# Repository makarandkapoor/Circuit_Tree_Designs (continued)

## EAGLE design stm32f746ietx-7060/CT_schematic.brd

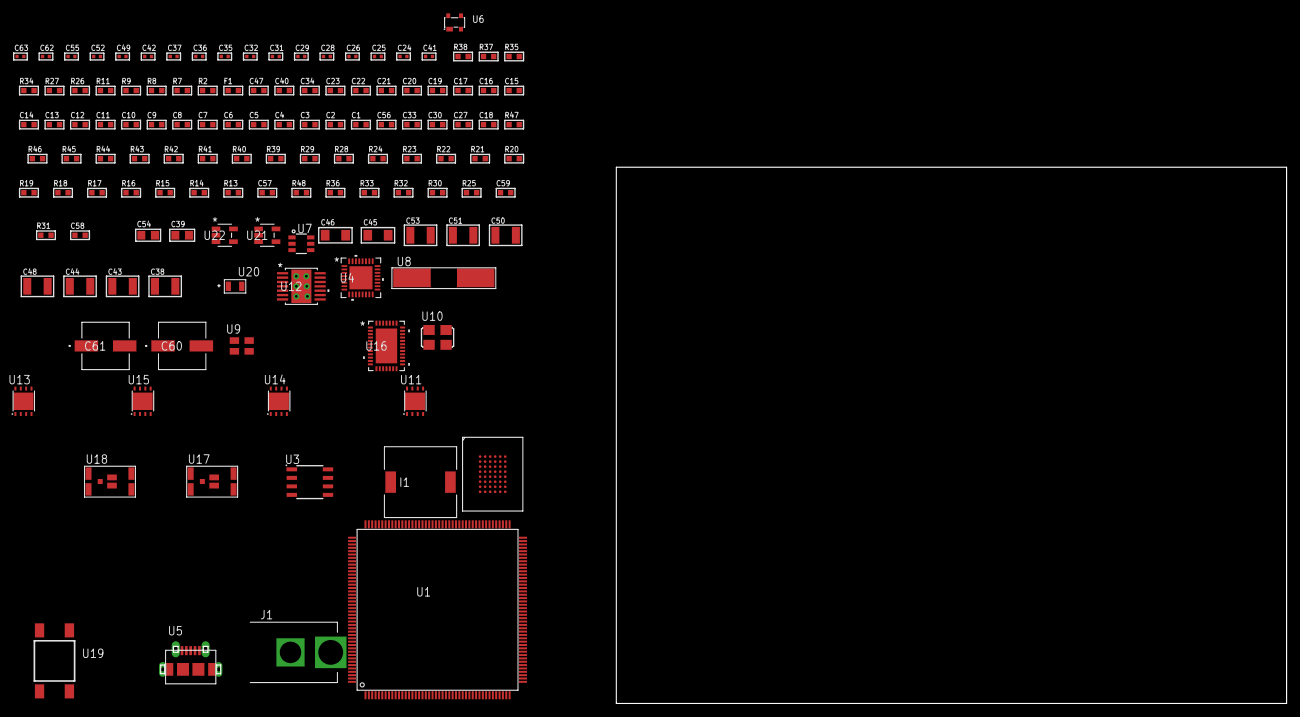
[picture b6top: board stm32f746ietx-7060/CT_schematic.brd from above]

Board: 2 copper layers, 129 parts (0 on the bottom side), 70 nets, no tracks yet.

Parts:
C1, C20, C34, C40: 1e-06; C0603
C2, C3, C4, C5, C6, C7, C8, C9, C10, C11, C12, C13, C14, C15, C16, C17, C21, C22, C23: 1e-07; C0603
C18: 4.7e-06; C0603
C19: 1e-08; C0603
C24, C25: 1e-11; C0402
C26, C29, C31, C32, C42, C55: 1e-07; C0402
C27, C30, C33, C56: 2.2e-06; C0603
C28, C35, C36, C37, C49, C52, C62, C63: 1e-08; C0402
C38, C48, C50, C51, C53: 1e-05; C1210
C39, C54: 1e-05; C0805
C41: 3.3e-09; C0402
C43, C44: 2.2e-05; C1210
C45, C46: 1e-05; C1206
C47: 8e-07; R0603
C57: 2.45e-08; R0603
C58: 2.8258362168397e-09; R0603
C59: 7.105e-09; R0603
C60, C61: 0.0001; EXV-9H
F1: 240.0; L0603
I1: 5.2e-06; DR1040
J1: PJ-037B; PJ-037B_PACKAGE
R2, R27, R35, R38: 1000.0; R0603
R7, R8: 4700.0; R0603
R9, R11: 2200.0; R0603
R13, R14, R15, R16, R17, R18, R19, R20, R21, R23, R24, R39, R41, R42, R45, R46, R47: 10000.0; R0603
R22: 47000.0; R0603
R25, R30, R32, R33, R36: 100000.0; R0603
R26, R37: 200.0; R0603
R28: 30000.0; R0603
R29: 22000.0; R0603
R31: 153694.38; R0603
R34: 3900.0; R0603
R40: 75000.0; R0603
R43, R44: 95300.0; R0603
R48: 120000.0; R0603
U1: STM32F746IET6; LQFP176
U2: IS61WV102416BLL-10MLI
U3: 24AA1025T-I/SN; SOIC-8
U4: TUSB1210BRHBR; RHB32_3P45X3P45
U5: 47590-0001; MICRO_USB_AB
U6: prtr5v0u2ax; SOT143B
U7: MAX4995AAUT+T; SOT-23-6
U8: ABLS-25.000MHZ-B2F-T
U9: ASEK-32.768KHz-ECST; ASEK
U10: ASFL1-26MHZ-NCS; ASFL1
U11, U14, U15: LP3878SDX-ADJ/NOPB; WSON-8
U12: tps54225PWP; HTSSOP14
U13: LP2951ACSDX/NOPB; WSON-8
U16: LTC2928CUHF#PBF; QFN-38_UHF
U17, U18: IRF8306MTRPbF; IRF8306MTRPBF
U19: 4-1437565-2; SW_4-1437565-2
U20: Q65110A2395; LGM67K-G1J2-24-Z
U21, U22: nc7sz125m5x; NC7SZ125M5X

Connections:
CLK_CRYSTAL_U1_29: C24.1, U1.29, U8.1
CLK_CRYSTAL_U1_30: C25.1, U1.30, U8.2
CLK_U1_9: U1.9, U9.3
CLK_U4_1: U4.1, U10.3
GND: C1.2, C2.2, C3.2, C4.2, C5.2, C6.2, C7.2, C8.2, C9.2, C10.2, C11.2, C12.2, C13.2, C14.2, C15.2, C16.2, C17.2, C18.2, C19.2, C20.2, C21.2, C22.2, C23.2, C24.2, C25.2, C26.2, C27.2, C28.2, C29.2, C30.2, C31.2, C32.2, C33.2, C34.2, C35.2, C36.2, C37.2, C38.2, C39.2, C40.2, C41.2, C43.2, C44.2, C45.2, C46.2, C47.2, C48.2, C49.2, C50.2, C51.2, C52.2, C53.2, C54.2, C55.2, C56.2, C57.2, C58.2, C59.2, C60.2, C61.2, C62.2, C63.2, J1.2, R2.2, R13.2, R21.2, R22.2, R27.2, R29.2, R32.2, R35.2, R38.2, R40.2, R43.2, R44.2, R45.2, R46.2, R47.2, U1.14, U1.22, U1.37, U1.61, U1.71, U1.90, U1.102, U1.113, U1.126, U1.135, U1.148, U1.158, U2.D1, U2.E6, U3.4, U3.7, U4.33, U5.5, U5.6, U5.7, U5.8, U5.9, U6.1, U7.2, U9.2, U10.2, U11.3, U11.PAD, U12.5, U12.8, U12.9, U12.15, U13.3, U13.4, U13.PAD, U14.3, U14.PAD, U15.3, U15.PAD, U16.8, U16.9, U16.10, U16.12, U16.13, U16.24, U16.25, U16.30, U16.32, U16.39, U20.C, U21.1, U21.3, U22.1, U22.3
NET_U1_31: R7.1, U1.31, U21.4
NET_U1_39: C19.1, C20.1, F1.1, U1.38, U1.39
NET_U1_48: R15.1, U1.48
NET_U1_125: C23.1, U1.125
NET_U1_164: R9.1, U1.164, U3.6
NET_U1_165: R11.1, U1.165, U3.5
NET_U1_166: R13.1, U1.166
NET_U1_171: R14.1, U1.171
NET_U1_176: U19.3, U19.4
NET_U2_A2: R17.1, U2.A2
NET_U2_B5: R16.1, U2.B5
NET_U2_G5: R18.1, U2.G5
NET_U3_1: R20.1, U3.1
NET_U3_2: R21.1, U3.2
NET_U3_3: R19.1, U3.3
NET_U4_11: R23.1, U4.11
NET_U4_12: C33.1, U4.12
NET_U4_14: R24.1, U4.14
NET_U4_20: C30.1, U4.20
NET_U4_27: R8.1, U4.27, U22.4
NET_U5_1: C34.1, U4.22, U5.1, U6.4, U7.1
NET_U5_2: U4.19, U5.2, U6.3
NET_U5_3: U4.18, U5.3, U6.2
NET_U5_4: U4.23, U5.4
NET_U7_3: R22.1, U7.3
NET_U7_4: U4.17, U7.4
NET_U11_1: C37.1, U11.1
NET_U11_6: R26.2, R27.1, U11.6
NET_U11_8: R25.1, U11.8
NET_U12_2: R28.2, R29.1, U12.2
NET_U12_3: C40.1, U12.3
NET_U12_4: C41.1, U12.4
NET_U12_10: C42.1, I1.1, U12.10, U12.11
NET_U12_12: C42.2, U12.12
NET_U13_5: R30.1, U13.5
NET_U13_7: R31.2, R32.1, U13.7
NET_U14_1: C49.1, U14.1
NET_U14_6: R34.2, R35.1, U14.6
NET_U14_8: R33.1, U14.8
NET_U15_1: C52.1, U15.1
NET_U15_6: R37.2, R38.1, U15.6
NET_U15_8: R36.1, U15.8
NET_U16_3: R46.1, U16.3
NET_U16_6: R43.1, U16.6
NET_U16_7: R44.1, U16.7
NET_U16_16: R45.1, R48.1, U16.16
NET_U16_18: R42.1, U16.18
NET_U16_19: R41.1, U16.19, U16.20
NET_U16_21: R39.1, R40.1, U16.21, U21.2, U22.2
NET_U16_22: C55.1, R39.2, R41.2, R42.2, U16.11, U16.22
NET_U16_26: C58.1, U16.26
NET_U16_27: C57.1, U16.27
NET_U16_28: C59.1, U16.28
NET_U16_38: R47.1, U16.38
NET_U17_3: U16.2, U17.3
NET_U18_3: U16.37, U18.3
NET_U19_1: R2.1, U19.1, U19.2
VCC_14V5: C56.1, C60.1, C61.1, J1.1, R48.2, U16.23, U17.1, U17.2, U17.6, U17.7, U18.1, U18.2, U18.6, U18.7
VCC_S1_14V5: C38.1, C45.1, C46.1, C47.1, C50.1, R25.2, R33.2, U11.4, U12.7, U12.13, U12.14, U13.8, U14.4, U17.4, U17.5
VCC_S2_14V5: C53.1, R36.2, U15.4, U18.4, U18.5
VCC_TIER1_1V2: C22.1, C39.1, R26.1, U1.81, U11.5
VCC_TIER1_1V8: C1.1, C2.1, C3.1, C4.1, C5.1, C6.1, C7.1, C8.1, C9.1, C10.1, C11.1, C12.1, C13.1, C14.1, C15.1, C16.1, C17.1, C18.1, C28.1, C31.1, C32.1, C43.1, C44.1, C62.1, C63.1, F1.2, I1.2, R7.2, R8.2, R9.2, R11.2, R14.2, R15.2, R19.2, R20.2, R23.2, R24.2, R28.1, U1.6, U1.15, U1.23, U1.36, U1.49, U1.62, U1.72, U1.82, U1.91, U1.103, U1.127, U1.136, U1.149, U1.159, U1.172, U3.8, U4.28, U4.30, U4.32, U12.1, U21.5, U22.5
VCC_TIER1_3V3: C21.1, C26.1, C27.1, C29.1, C35.1, C36.1, C48.1, R16.2, R17.2, R18.2, R30.2, R31.1, U1.114, U2.D6, U2.E1, U4.21, U9.4, U10.4, U13.1
VCC_TIER1_5V0: C51.1, R34.1, U7.5, U14.5
VCC_TIER2_1V2: C54.1, R37.1, U15.5

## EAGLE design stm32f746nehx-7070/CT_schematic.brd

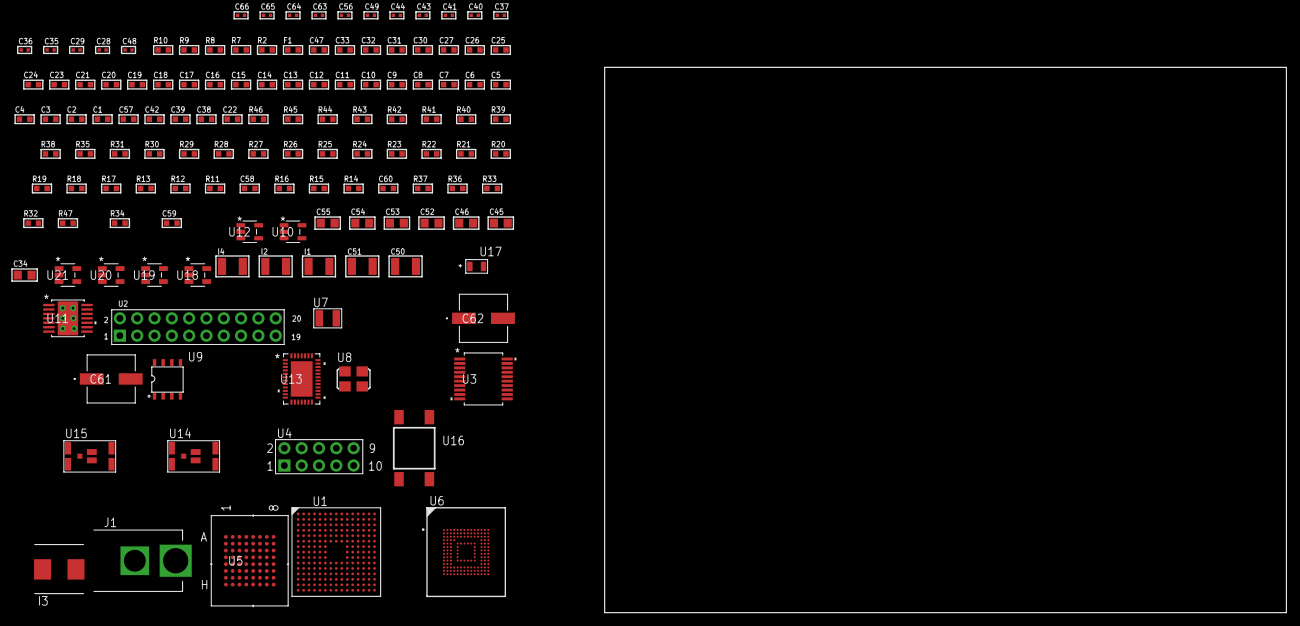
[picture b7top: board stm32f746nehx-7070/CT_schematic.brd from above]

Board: 2 copper layers, 100.0 x 80.0 mm, 135 parts (0 on the bottom side), 130 nets, no tracks yet.

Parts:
C1, C24, C30, C31, C32, C33, C47: 1e-06; C0603
C2, C3, C4, C5, C6, C7, C8, C9, C10, C11, C12, C13, C14, C15, C16, C17, C18, C19, C20, C21, C25, C26, C27: 1e-07; C0603
C22: 4.7e-06; C0603
C23: 1e-08; C0603
C28, C29: 1e-11; C0402
C34: 4.7e-06; C0805
C35, C36, C43, C44, C63, C64, C65, C66: 1e-08; C0402
C37, C40, C41, C49, C56: 1e-07; C0402
C38, C39, C42, C57: 2.2e-06; C0603
C45, C46, C52, C53, C54, C55: 1e-05; C0805
C48: 3.3e-09; C0402
C50, C51: 2.2e-05; C1210
C58: 2.45e-08; R0603
C59: 2.8258362168397e-09; R0603
C60: 7.105e-09; R0603
C61, C62: 0.0001; EXV-9H
F1: 240.0; L0603
I1, I2, I4: 1.5e-05; L1210
I3: 3.3e-06; WE-HCI_7030/7040/7050
J1: PJ-037B; PJ-037B_PACKAGE
R2: 1000.0; R0603
R7, R8, R9, R10: 4700.0; R0603
R11, R12, R13, R17, R18, R19, R20, R21, R38, R40, R41, R44, R45, R46: 10000.0; R0603
R14, R15, R16: 100000.0; R0603
R22, R23, R24, R25, R26, R27, R28, R29, R30, R31: 34000.0; R0603
R32, R33, R36, R37: 1000000.0; R0603
R34: 71007.101651032; R0603
R35: 22000.0; R0603
R39: 75000.0; R0603
R42, R43: 95300.0; R0603
R47: 36527.272727273; R0603
U1: STM32F746NEH6; TFBGA216
U2: arducam_ov2640; ARDUCAM
U3: MAX3218EAP+T; SSOP-20
U4: HTSS-105-01-G-D
U5: mt28ew512aba1HPC-0AAT; LBGA-64
U6: mtfc4gmcdm; TFBGA-153
U7: ABS07-32.768KHZ-7-T
U8: ASFL1-25MHZ-NCS; ASFL1
U9: idt74fct38072; IDT74FCT38072
U10, U12: ltc3406es5; TSOT-23-5
U11: tps54225PWP; HTSSOP14
U13: LTC2928CUHF#PBF; QFN-38_UHF
U14, U15: IRF8306MTRPbF; IRF8306MTRPBF
U16: 4-1437565-2; SW_4-1437565-2
U17: Q65110A2395; LGM67K-G1J2-24-Z
U18, U19, U20, U21: nc7sz125m5x; NC7SZ125M5X

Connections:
CLK_CRYSTAL_U1_E1: C28.1, U1.E1, U7.1
CLK_CRYSTAL_U1_F1: C29.1, U1.F1, U7.2
CLK_U1_G1: U1.G1, U9.6
CLK_U2_8: U2.8, U9.7
CLK_U9_3: U8.3, U9.3
GND: C1.2, C2.2, C3.2, C4.2, C5.2, C6.2, C7.2, C8.2, C9.2, C10.2, C11.2, C12.2, C13.2, C14.2, C15.2, C16.2, C17.2, C18.2, C19.2, C20.2, C21.2, C22.2, C23.2, C24.2, C25.2, C26.2, C27.2, C28.2, C29.2, C30.2, C31.2, C32.2, C33.2, C35.2, C36.2, C37.2, C38.2, C39.2, C40.2, C41.2, C42.2, C43.2, C44.2, C45.2, C46.1, C46.2, C47.2, C48.2, C50.2, C51.2, C52.2, C53.2, C54.2, C55.1, C55.2, C56.2, C57.2, C58.2, C59.2, C60.2, C61.2, C62.2, C63.2, C64.2, C65.2, C66.2, J1.2, R2.2, R11.2, R32.2, R35.2, R36.2, R39.2, R42.2, R43.2, R44.2, R45.2, R46.2, U1.F2, U1.F6, U1.F7, U1.F8, U1.F9, U1.F10, U1.G6, U1.G10, U1.H6, U1.H10, U1.J6, U1.J10, U1.K6, U1.K7, U1.K8, U1.K9, U1.K10, U1.L6, U1.M1, U1.N1, U2.2, U2.20, U3.5, U3.17, U3.20, U4.9, U5.E8, U5.H2, U5.H7, U6.C4, U6.E7, U6.G5, U6.H10, U6.K8, U6.N2, U6.N5, U6.P4, U6.P6, U8.2, U9.4, U9.5, U9.8, U10.2, U11.5, U11.8, U11.9, U11.15, U12.2, U13.8, U13.9, U13.10, U13.12, U13.13, U13.24, U13.25, U13.30, U13.32, U13.39, U17.C, U18.1, U18.3, U19.1, U19.3, U20.1, U20.3, U21.1, U21.3
NET_U1_E5: R12.1, U1.E5
NET_U1_E6: R11.1, U1.E6
NET_U1_E11: C27.1, U1.E11
NET_U1_J1: R9.1, U1.J1, U20.4
NET_U1_L5: R13.1, U1.L5
NET_U1_R1: C23.1, C24.1, F1.1, U1.P1, U1.R1
NET_U1_R15: U16.3, U16.4
NET_U2_19: R10.1, U2.19, U21.4
NET_U3_1: I1.1, U3.1
NET_U3_2: R14.1, U3.2
NET_U3_3: R15.1, U3.3
NET_U3_4: R16.1, U3.4
NET_U3_15: C33.1, U3.15
NET_U3_16: C34.2, U3.16
NET_U3_18: C34.1, U3.18
NET_U3_19: C32.1, U3.19
NET_U4_3: U3.12, U4.3
NET_U4_4: U3.11, U4.4
NET_U4_5: U3.14, U4.5
NET_U4_6: U3.13, U4.6
NET_U5_B4: R20.1, U5.B4
NET_U5_B5: R7.1, U5.B5, U18.4
NET_U6_C2: C39.1, C40.1, U6.C2
NET_U6_K5: R8.1, U6.K5, U19.4
NET_U10_3: I2.1, U10.3
NET_U10_5: R32.1, R33.1, U10.5
NET_U10_ATNET_3: I2.2, R33.2
NET_U11_2: R34.2, R35.1, U11.2
NET_U11_3: C47.1, U11.3
NET_U11_4: C48.1, U11.4
NET_U11_10: C49.1, I3.1, U11.10, U11.11
NET_U11_12: C49.2, U11.12
NET_U12_3: I4.1, U12.3
NET_U12_5: R36.1, R37.1, U12.5
NET_U12_ATNET_3: I4.2, R37.2
NET_U13_3: R45.1, U13.3
NET_U13_6: R42.1, U13.6
NET_U13_7: R43.1, U13.7
NET_U13_16: R44.1, R47.1, U13.16
NET_U13_18: R41.1, U13.18
NET_U13_19: R40.1, U13.19, U13.20
NET_U13_21: R38.1, R39.1, U13.21, U18.2, U19.2, U20.2, U21.2
NET_U13_26: C59.1, U13.26
NET_U13_27: C58.1, U13.27
NET_U13_28: C60.1, U13.28
NET_U13_38: R46.1, U13.38
NET_U14_3: U13.2, U14.3
NET_U15_3: U13.37, U15.3
NET_U16_1: R2.1, U16.1, U16.2
PROC_DCMI_D0: U1.E15, U2.18
PROC_DCMI_D1: U1.D15, U2.17
PROC_DCMI_D2: U1.C8, U2.16
PROC_DCMI_D3: U1.A5, U2.15
PROC_DCMI_D4: U1.E13, U2.14
PROC_DCMI_D5: U1.B6, U2.13
PROC_DCMI_D6: U1.D6, U2.12
PROC_DCMI_D7: U1.D4, U2.11
PROC_DCMI_D8: U1.D14, U2.10
PROC_DCMI_D9: U1.C14, U2.9
PROC_DCMI_HSYNC: U1.N4, U2.6
PROC_DCMI_PIXCLK: U1.P3, U2.7
PROC_DCMI_VSYNC: U1.B5, U2.5
PROC_FMC_A0: U1.D2, U5.E2
PROC_FMC_A1: U1.E2, U5.D2
PROC_FMC_A2: U1.G2, U5.C2
PROC_FMC_A3: U1.H2, U5.A2
PROC_FMC_A4: U1.J2, U5.B2
PROC_FMC_A5: U1.K3, U5.D3
PROC_FMC_A6: U1.M6, U5.C3
PROC_FMC_A7: U1.N6, U5.A3
PROC_FMC_A8: U1.P6, U5.B6
PROC_FMC_A9: U1.M8, U5.A6
PROC_FMC_A10: U1.N7, U5.C6
PROC_FMC_A11: U1.M7, U5.D6
PROC_FMC_A12: U1.M13, U5.B7
PROC_FMC_A13: U1.M12, U5.A7
PROC_FMC_A14: U1.N12, U5.C7
PROC_FMC_A15: U1.N11, U5.D7
PROC_FMC_A16: U1.N10, U5.E7
PROC_FMC_A17: U1.M10, U5.B3
PROC_FMC_A18: U1.M11, U5.C4
PROC_FMC_A19: U1.A2, U5.D5
PROC_FMC_A20: U1.A1, U5.D4
PROC_FMC_A21: U1.B1, U5.C5
PROC_FMC_A22: U1.B2, U5.B8
PROC_FMC_A23: U1.A3, U5.C8
PROC_FMC_A24: U1.B3, U5.F8
PROC_FMC_D0: U1.L12, U5.E3
PROC_FMC_D1: U1.K13, U5.H3
PROC_FMC_D2: U1.B12, U5.E4
PROC_FMC_D3: U1.C12, U5.H4
PROC_FMC_D4: U1.R8, U5.H5
PROC_FMC_D5: U1.N9, U5.E5
PROC_FMC_D6: U1.P9, U5.H6
PROC_FMC_D7: U1.R9, U5.E6
PROC_FMC_D8: U1.P10, U5.F3
PROC_FMC_D9: U1.R10, U5.G3
PROC_FMC_D10: U1.R12, U5.F4
PROC_FMC_D11: U1.P11, U5.G4
PROC_FMC_D12: U1.R11, U5.F5
PROC_FMC_D13: U1.L15, U5.G6
PROC_FMC_D14: U1.L14, U5.F6
PROC_FMC_D15: U1.K15, U5.G7
PROC_FMC_NBL0: R21.1, U1.A6, U5.F7
PROC_FMC_NE2: R17.1, U1.D9, U5.F2
PROC_FMC_NOE: R18.1, U1.D11, U5.G2
PROC_FMC_NWAIT: U1.B11, U5.A4
PROC_FMC_NWE: R19.1, U1.C10, U5.A5
PROC_SDMMC1_CK: R31.1, U1.A12, U6.M6
PROC_SDMMC1_CMD: R30.1, U1.D12, U6.M5
PROC_SDMMC1_D0: R22.1, U1.G14, U6.A3
PROC_SDMMC1_D1: R23.1, U1.F14, U6.A4
PROC_SDMMC1_D2: R24.1, U1.B14, U6.A5
PROC_SDMMC1_D3: R25.1, U1.B13, U6.B2
PROC_SDMMC1_D4: R26.1, U1.A7, U6.B3
PROC_SDMMC1_D5: R27.1, U1.B4, U6.B4
PROC_SDMMC1_D6: R28.1, U1.H15, U6.B5
PROC_SDMMC1_D7: R29.1, U1.G15, U6.B6
VCC_5V2: C56.1, C57.1, C61.1, C62.1, J1.1, R38.2, R40.2, R41.2, R47.2, U13.11, U13.22, U14.1, U14.2, U14.6, U14.7, U15.1, U15.2, U15.6, U15.7
VCC_S1_5V2: C45.1, C52.1, C53.1, U10.4, U11.7, U11.13, U11.14, U14.4, U14.5
VCC_S2_5V2: C54.1, U12.4, U15.4, U15.5
VCC_TIER1_1V2: C26.1, C46.2, I2.2, R33.2, U1.L11
VCC_TIER1_3V3: C1.1, C2.1, C3.1, C4.1, C5.1, C6.1, C7.1, C8.1, C9.1, C10.1, C11.1, C12.1, C13.1, C14.1, C15.1, C16.1, C17.1, C18.1, C19.1, C20.1, C21.1, C22.1, C25.1, C30.1, C31.1, C35.1, C36.1, C37.1, C38.1, C41.1, C42.1, C43.1, C44.1, C50.1, C51.1, C63.1, C64.1, C65.1, C66.1, F1.2, I1.2, I3.2, R7.2, R8.2, R9.2, R10.2, R12.2, R13.2, R14.2, R15.2, R16.2, R17.2, R18.2, R19.2, R20.2, R21.2, R22.2, R23.2, R24.2, R25.2, R26.2, R27.2, R28.2, R29.2, R30.2, R31.2, R34.1, U1.C1, U1.E7, U1.E8, U1.E9, U1.E10, U1.F4, U1.F5, U1.F11, U1.G5, U1.G11, U1.H5, U1.H11, U1.J5, U1.J11, U1.K5, U1.K11, U1.L7, U1.L8, U1.L9, U1.L10, U2.1, U3.6, U5.D8, U5.F1, U5.G5, U6.C6, U6.E6, U6.F5, U6.J10, U6.K9, U6.M4, U6.N4, U6.P3, U6.P5, U8.4, U9.1, U9.2, U11.1, U18.5, U19.5, U20.5, U21.5
VCC_TIER2_1V2: C55.2, I4.2, R37.2

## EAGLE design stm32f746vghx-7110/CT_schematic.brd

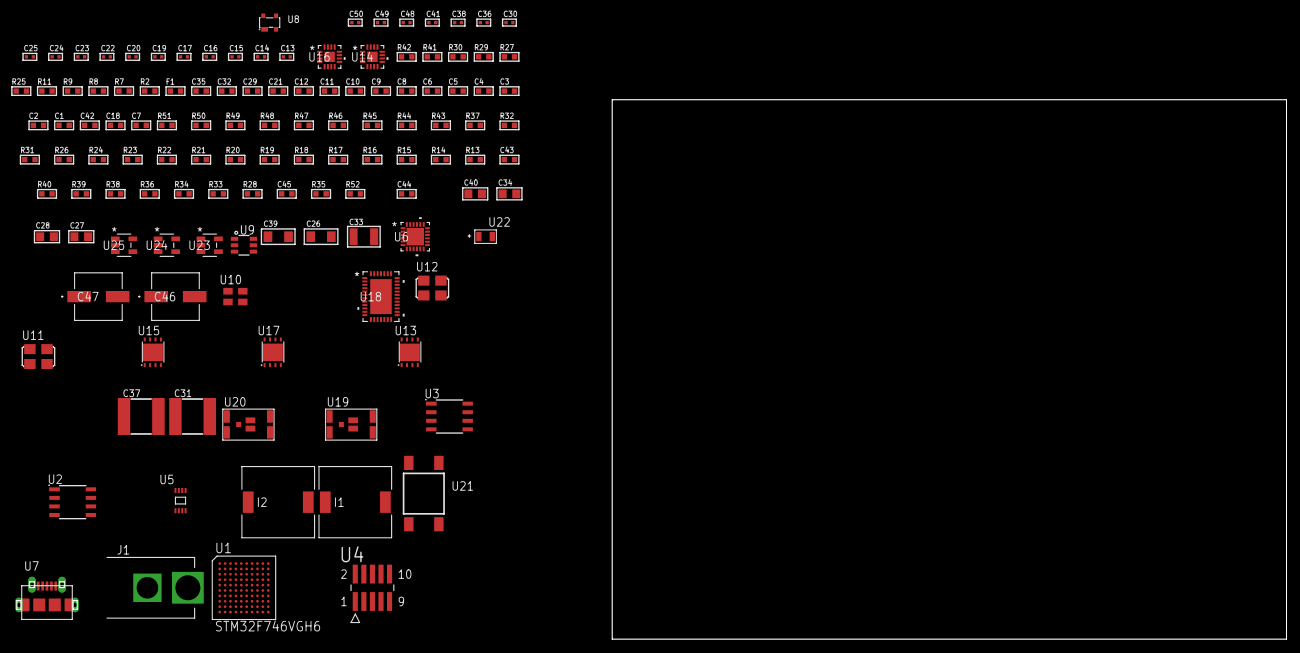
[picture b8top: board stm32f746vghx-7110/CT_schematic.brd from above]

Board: 2 copper layers, 124 parts (0 on the bottom side), 93 nets, no tracks yet.

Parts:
C1, C9, C21, C29, C32, C35: 1e-06; C0603
C2, C3, C4, C5, C6, C10, C11, C12: 1e-07; C0603
C7: 4.7e-06; C0603
C8: 1e-08; C0603
C13, C14, C16, C17, C19, C20, C22, C23, C24, C25, C38, C48, C49, C50: 1e-08; C0402
C15, C30, C36, C41: 1e-07; C0402
C18, C42: 2.2e-06; C0603
C26, C39: 1e-05; C1206
C27, C28, C34, C40: 1e-05; C0805
C31, C37: 6.8e-05; 2220
C33: 1e-05; C1210
C43: 2.45e-08; R0603
C44: 2.8258362168397e-09; R0603
C45: 7.105e-09; R0603
C46, C47: 0.0001; EXV-9H
F1: 240.0; L0603
I1, I2: 2.5e-06; DR1040
J1: PJ-037B; PJ-037B_PACKAGE
R2, R30, R42: 1000.0; R0603
R7, R8: 4700.0; R0603
R9, R11: 2200.0; R0603
R13, R14, R15, R16, R17, R18, R19, R20, R21, R22, R23, R24, R43, R45, R46, R49, R50, R51: 10000.0; R0603
R25: 5.0; R0603
R26: 47000.0; R0603
R27: 8060.0; R0603
R28, R34, R36, R40: 100000.0; R0603
R29, R41: 200.0; R0603
R31, R37: 20000.0; R0603
R32: 39000.0; R0603
R33, R39: 300000.0; R0603
R35: 153694.38; R0603
R38: 150000.0; R0603
R44: 75000.0; R0603
R47, R48: 95300.0; R0603
R52: 40981.818181818; R0603
U1: STM32F746VGH6; TFBGA100
U2: AT25080B-SSHL-T; SOIC-8
U3: AT25256B-SSHL-T; SOIC-8
U4: FTSH-105-01-L-DV-K; SAMTEC_FTSH-105-01-L-DV-K
U5: 24AA04-I/MC; TDFN-8/6MM
U6: USB3317C-CP-TR; QFN-24
U7: 47590-0001; MICRO_USB_AB
U8: prtr5v0u2ax; SOT143B
U9: MAX4995AAUT+T; SOT-23-6
U10: ASEK-32.768KHz-ECST; ASEK
U11: ASFL1-25MHZ-NCS; ASFL1
U12: ASFL1-26MHZ-NCS; ASFL1
U13, U17: LP3878SDX-ADJ/NOPB; WSON-8
U14, U16: LTC3601EUD#PBF; QFN-16_EP
U15: LP2951ACSDX/NOPB; WSON-8
U18: LTC2928CUHF#PBF; QFN-38_UHF
U19, U20: IRF8306MTRPbF; IRF8306MTRPBF
U21: 4-1437565-2; SW_4-1437565-2
U22: Q65110A2395; LGM67K-G1J2-24-Z
U23, U24, U25: nc7sz125m5x; NC7SZ125M5X

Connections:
CLK_U1_A1: U1.A1, U10.3
CLK_U1_C1: U1.C1, U11.3
CLK_U6_23: U6.23, U12.3
GND: C1.2, C2.2, C3.2, C4.2, C5.2, C6.2, C7.2, C8.2, C9.2, C10.2, C11.2, C12.2, C13.2, C14.2, C15.2, C16.2, C17.2, C18.2, C19.2, C20.2, C21.2, C22.2, C23.2, C24.2, C25.2, C26.2, C27.2, C28.2, C29.2, C31.1, C31.2, C32.2, C33.2, C34.2, C35.2, C37.1, C37.2, C38.2, C39.2, C40.2, C41.2, C42.2, C43.2, C44.2, C45.2, C46.2, C47.2, C48.2, C49.2, C50.2, J1.2, R2.2, R13.2, R25.2, R26.2, R27.2, R30.2, R31.2, R33.2, R36.2, R37.2, R39.2, R42.2, R44.2, R47.2, R48.2, R49.2, R50.2, R51.2, U1.C2, U1.E4, U1.E5, U1.G1, U1.J1, U2.4, U3.4, U4.3, U4.5, U5.4, U6.25, U7.5, U7.6, U7.7, U7.8, U7.9, U8.1, U9.2, U10.2, U11.2, U12.2, U13.3, U13.PAD, U14.1, U14.9, U14.17, U15.3, U15.4, U15.PAD, U16.1, U16.9, U16.17, U17.3, U17.PAD, U18.8, U18.9, U18.10, U18.12, U18.13, U18.24, U18.25, U18.30, U18.32, U18.39, U22.C, U23.2, U23.3, U24.1, U24.3, U25.1, U25.3
NET_U1_A4: R11.1, U1.A4, U5.5
NET_U1_B4: R9.1, U1.B4, U5.6
NET_U1_D5: R13.1, U1.D5
NET_U1_E1: R7.1, U1.E1, U24.4
NET_U1_E6: R15.1, U1.E6
NET_U1_E7: C12.1, U1.E7
NET_U1_F7: R14.1, U1.F7
NET_U1_H1: C8.1, C9.1, F1.1, U1.H1
NET_U1_K10: U21.3, U21.4
NET_U2_3: R16.1, U2.3
NET_U2_7: R18.1, U2.7
NET_U3_3: R19.1, U3.3
NET_U3_7: R21.1, U3.7
NET_U4_9: R25.1, U4.9
NET_U6_4: C18.1, U6.4
NET_U6_22: R8.1, U6.22, U25.4
NET_U6_24: R27.1, U6.24
NET_U7_1: C21.1, U6.2, U7.1, U8.4, U9.1
NET_U7_2: U6.5, U7.2, U8.3
NET_U7_3: U6.6, U7.3, U8.2
NET_U7_4: U6.1, U7.4
NET_U9_3: R26.1, U9.3
NET_U9_4: U6.7, U9.4
NET_U13_1: C25.1, U13.1
NET_U13_6: R29.2, R30.1, U13.6
NET_U13_8: R28.1, U13.8
NET_U14_3: C30.2, I1.1, U14.3, U14.4
NET_U14_6: C30.1, U14.6
NET_U14_7: C29.1, U14.7, U14.12
NET_U14_10: R33.1, U14.10
NET_U14_11: R31.1, R32.1, U14.11
NET_U14_ATNET_3: I1.2, R32.2
NET_U15_5: R34.1, U15.5
NET_U15_7: R35.2, R36.1, U15.7
NET_U16_3: C36.2, I2.1, U16.3, U16.4
NET_U16_6: C36.1, U16.6
NET_U16_7: C35.1, U16.7, U16.12
NET_U16_10: R39.1, U16.10
NET_U16_11: R37.1, R38.1, U16.11
NET_U16_ATNET_3: I2.2, R38.2
NET_U17_1: C38.1, U17.1
NET_U17_6: R41.2, R42.1, U17.6
NET_U17_8: R40.1, U17.8
NET_U18_3: R50.1, U18.3
NET_U18_6: R47.1, U18.6
NET_U18_7: R48.1, U18.7
NET_U18_16: R49.1, R52.1, U18.16
NET_U18_18: R46.1, U18.18
NET_U18_19: R45.1, U18.19, U18.20
NET_U18_21: R43.1, R44.1, U18.21, U23.4, U24.2, U25.2
NET_U18_26: C44.1, U18.26
NET_U18_27: C43.1, U18.27
NET_U18_28: C45.1, U18.28
NET_U18_38: R51.1, U18.38
NET_U19_3: U18.2, U19.3
NET_U20_3: U18.37, U20.3
NET_U21_1: R2.1, U21.1, U21.2
PROC_SPI2_MISO: U1.H10, U2.2
PROC_SPI2_MOSI: U1.F2, U2.5
PROC_SPI2_NSS: R17.1, U1.A6, U2.1
PROC_SPI2_SCK: U1.C7, U2.6
PROC_SPI3_MISO: U1.B8, U3.2
PROC_SPI3_MOSI: U1.C6, U3.5
PROC_SPI3_NSS: R20.1, U1.A8, U3.1
PROC_SPI3_SCK: U1.B9, U3.6
PROC_SYS_JTCK_SWCLK: R23.1, U1.A9, U4.4
PROC_SYS_JTDO_SWO: U1.A7, U4.6
PROC_SYS_JTMS_SWDIO: R24.1, U1.A10, U4.2
PROC_USB_OTG_HS_ULPI_CK: U1.H3, U6.12
PROC_USB_OTG_HS_ULPI_D0: U1.K2, U6.16
PROC_USB_OTG_HS_ULPI_D1: U1.J4, U6.15
PROC_USB_OTG_HS_ULPI_D2: U1.K4, U6.14
PROC_USB_OTG_HS_ULPI_D3: U1.J7, U6.13
PROC_USB_OTG_HS_ULPI_D4: U1.K7, U6.11
PROC_USB_OTG_HS_ULPI_D5: U1.K8, U6.10
PROC_USB_OTG_HS_ULPI_D6: U1.J8, U6.9
PROC_USB_OTG_HS_ULPI_D7: U1.C5, U6.8
PROC_USB_OTG_HS_ULPI_DIR: U1.E2, U6.19
PROC_USB_OTG_HS_ULPI_NXT: U1.F3, U6.18
PROC_USB_OTG_HS_ULPI_STP: U1.F1, U6.20
RST_OUT_U4_JTAG_RST_B: R22.1, U4.10, U23.1
VCC_5V7: C41.1, C42.1, C46.1, C47.1, J1.1, R43.2, R45.2, R46.2, R52.2, U18.11, U18.22, U19.1, U19.2, U19.6, U19.7, U20.1, U20.2, U20.6, U20.7
VCC_S1_5V7: C26.1, C28.1, C32.1, C34.1, R28.2, U13.4, U14.15, U14.16, U15.8, U16.15, U16.16, U19.4, U19.5
VCC_S2_5V7: C39.1, R40.2, U17.4, U20.4, U20.5
VCC_TIER1_1V2: C11.1, C27.1, R29.1, U1.F8, U13.5
VCC_TIER1_1V8: C1.1, C2.1, C3.1, C4.1, C5.1, C6.1, C7.1, C13.1, C14.1, C15.1, C16.1, C19.1, C20.1, C31.2, C48.1, C49.1, C50.1, F1.2, I1.2, R7.2, R8.2, R9.2, R11.2, R14.2, R15.2, R16.2, R17.2, R18.2, R19.2, R20.2, R21.2, R22.2, R23.2, R24.2, R32.2, U1.B2, U1.D2, U1.F4, U1.F5, U1.K1, U2.8, U3.8, U4.1, U5.7, U5.8, U6.17, U6.21, U14.8, U23.5, U24.5, U25.5
VCC_TIER1_3V3: C10.1, C17.1, C22.1, C23.1, C24.1, C33.1, R34.2, R35.1, U1.F6, U6.3, U10.4, U11.4, U12.4, U15.1
VCC_TIER1_5V0: C37.2, I2.2, R38.2, U9.5, U16.8
VCC_TIER2_1V2: C40.1, R41.1, U17.5
